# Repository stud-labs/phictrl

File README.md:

# phictrl
Old Philips projector control module

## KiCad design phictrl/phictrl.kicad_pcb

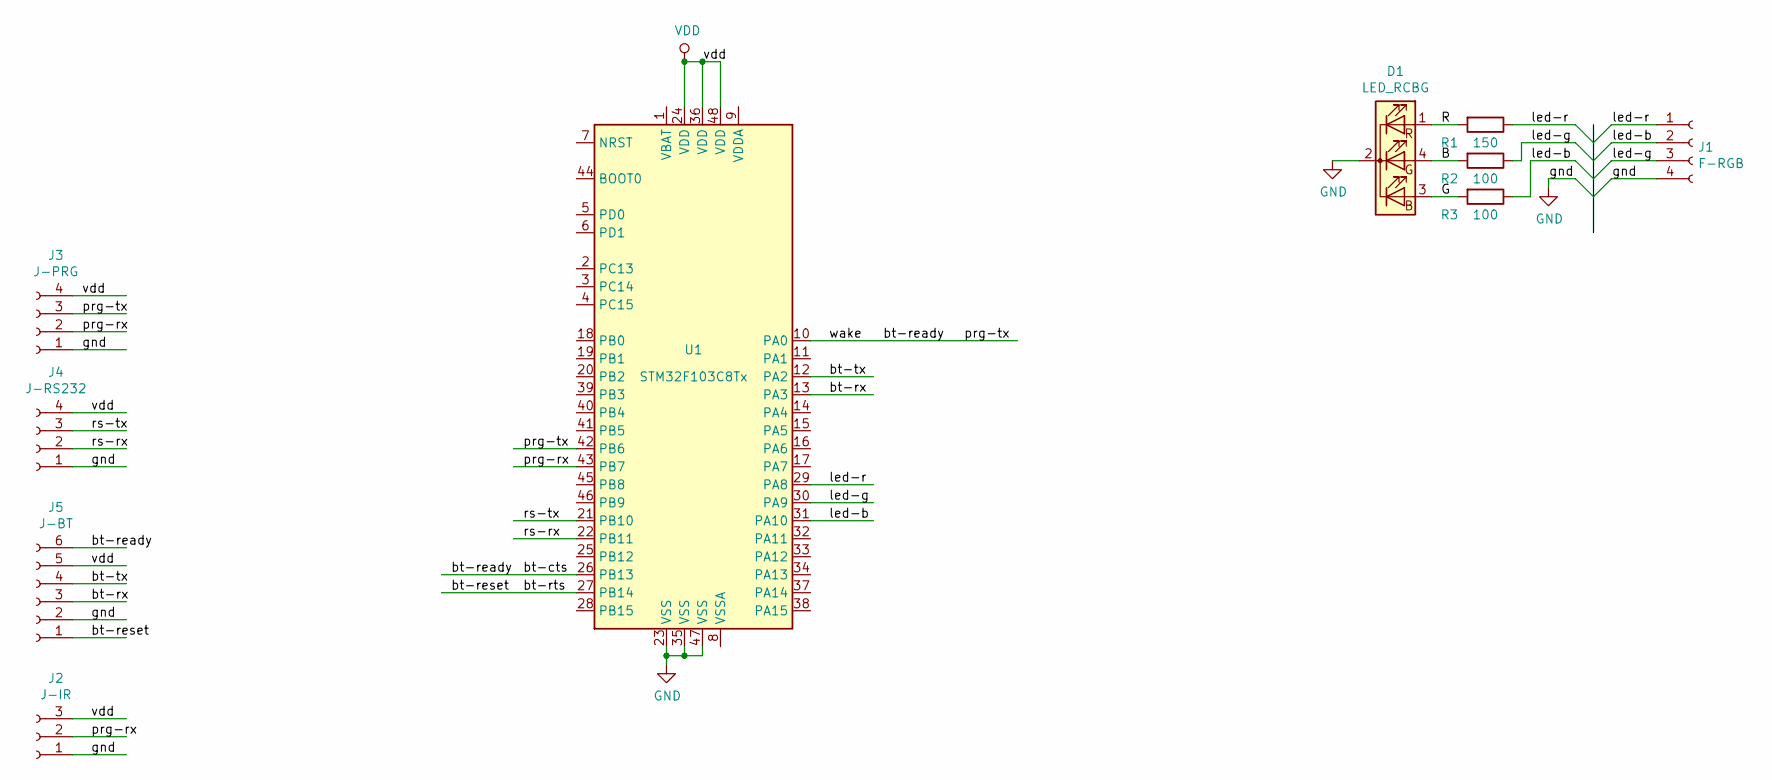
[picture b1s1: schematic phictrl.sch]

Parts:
D1: LED_RCBG; LED_D5.0mm-4_RGB
J1: F-RGB; SolderWirePad_1x04_P3.81mm_Drill1mm
J2: J-IR; PinHeader_1x03_P2.54mm_Vertical
J3: J-PRG; PinHeader_1x04_P2.54mm_Vertical
J4: J-RS232; PinHeader_1x04_P2.54mm_Vertical
J5: J-BT; PinHeader_1x06_P2.54mm_Vertical
R1: 150; R_0805_2012Metric_Pad1.15x1.40mm_HandSolder
R2, R3: 100; R_0805_2012Metric_Pad1.15x1.40mm_HandSolder
U1: STM32F103C8Tx; LQFP-48_7x7mm_P0.5mm

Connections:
/bt-cts: J3.3, J5.6, U1.10 (PA0), U1.26 (PB13), U1.42 (PB6)
/bt-reset: J5.1, U1.27 (PB14)
/bt-rx: J5.3, U1.13 (PA3)
/bt-tx: J5.4, U1.12 (PA2)
/led-b: J1.2, R3.1, U1.31 (PA10)
/led-g: J1.3, R2.1, U1.30 (PA9)
/led-r: J1.1, R1.1, U1.29 (PA8)
/prg-rx: J2.2, J3.2, U1.43 (PB7)
/rs-rx: J4.2, U1.22 (PB11)
/rs-tx: J4.3, U1.21 (PB10)
GND: D1.2 (K), J1.4, J2.1, J3.1, J4.1, J5.2, U1.23 (VSS), U1.35 (VSS), U1.47 (VSS)
unnamed: D1.1 (RA), R1.2
unnamed: D1.3 (BA), R3.2
unnamed: D1.4 (GA), R2.2
VDD: J2.3, J3.4, J4.4, J5.5, U1.24 (VDD), U1.36 (VDD), U1.48 (VDD)

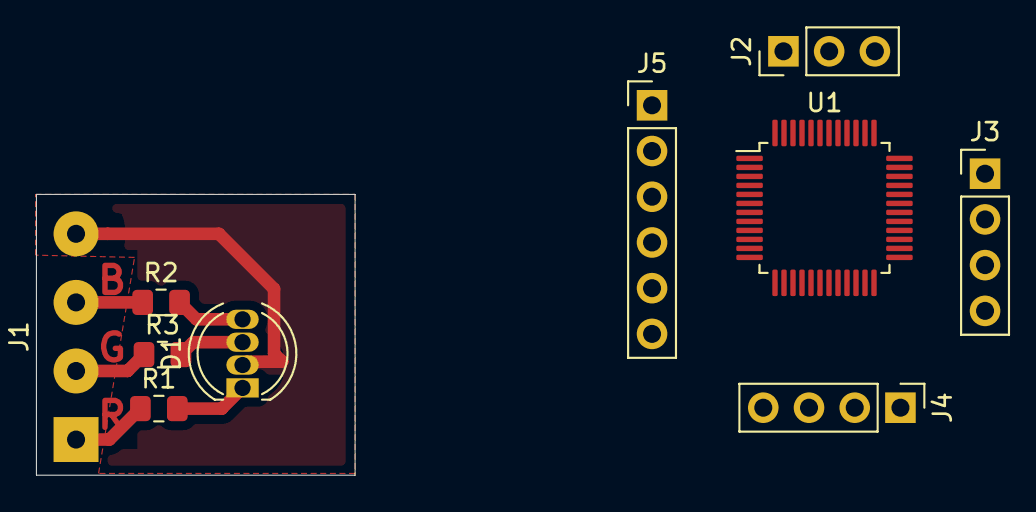
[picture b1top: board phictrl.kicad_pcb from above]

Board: 2 copper layers, 17.7 x 15.6 mm, 10 parts (0 on the bottom side), 15 nets.

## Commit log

2020-02-06 Initial import
2020-02-06 Planned pins and developed LED PCB.
2020-02-07 Some changes.
2020-02-08 Printed PCB
2020-02-09 Changet .gitignore.
2020-02-09 Added blink project.
2020-02-09 Set up of loading terminal.
2020-02-11 Try to implement blinky
2020-02-11 Added reference manual.
2020-02-11 Adjusted to blink with A6A7 or B0.
2020-02-12 Added timer delay library.
2020-02-12 Added FolkDocs stuff.
2020-02-12 Forgot to download epub.
2020-02-12 Added IR documantation.
2020-02-13 My implementation of GPIOs
2020-02-13 Refined the loading speed. Added service modules.
2020-02-14 Implementing bit setup
2020-02-14 Worked init!
2020-02-14 Implemented on/off LED output.
2020-02-15 Implemented blinking with parameters.
2020-02-15 More delay
2020-02-15 Implementing IR input.
2020-02-16 Some more code.
2020-02-17 Testing inputs
2020-02-17 Adding USART communication routines, compiler bug?
2020-02-17 Correct the connection speed.
2020-02-17 Extracted good part flashed, IR decoder reverse engineering.
2020-02-18 Added disassembler.
2020-02-21 Moving comm forward.
2020-02-21 Added System Timer interrupt handler routines.
2020-02-24 Added programming manual.
2020-02-24 Finished timer operation library.
2020-02-24 Added example photo.
2020-02-24 Added NEC decoder library.
2020-02-24 Added terminal bash script.
2020-02-24 Removed tail spaces.
2020-02-24 Ready EXTI pin setups.
2020-02-25 Finally, implemented ISR for PB4!
2020-02-25 Shifted prepared code to library.
2020-02-25 Shift disassembler to library.
2020-02-26 Added example for bt connection.
2020-02-26 Library source reconfiguration.
2020-02-26 Implemented decoding of IR.
2020-02-26 Tried to setup comm. It ignores writes.
2020-02-26 Now I can receive characters. Need setup alternate function for TX USART2.
2020-02-27 Removed unused stuff.
2020-02-28 Added some non working code for interrupt.
2020-02-28 Commented out setup of IRQ for USART2
2020-02-29 Added PANASONIC Projector Doc.
2020-03-07 Fixed stack faults when whole decoding has done. TODO: fix repeats.
2020-03-07 Aligned stack in nec.key word. TODO: implement repeats.
